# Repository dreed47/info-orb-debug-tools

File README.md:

# info-orb-debug-tools

- a version of info orb PCB that does not use pins 12, 13, 14, 15 and adds an IDC connector to connect a JTAG adapter for breakpoint debugging

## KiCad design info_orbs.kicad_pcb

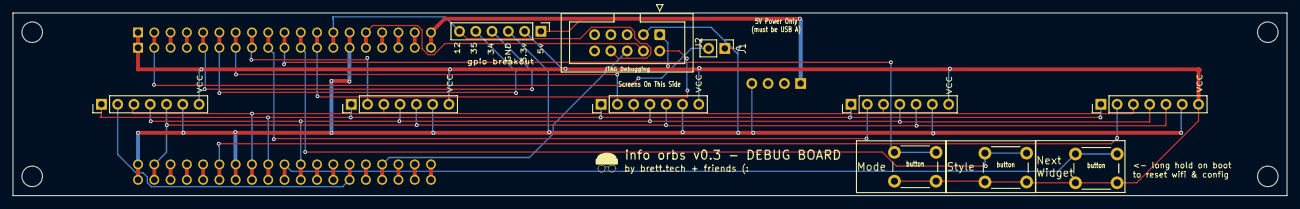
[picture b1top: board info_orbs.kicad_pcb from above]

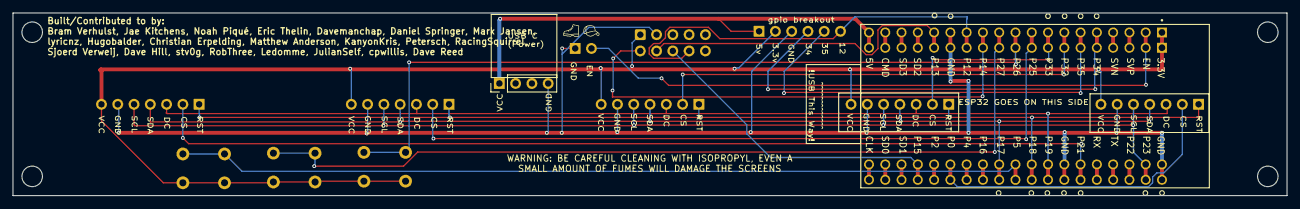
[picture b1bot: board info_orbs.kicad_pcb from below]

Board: 2 copper layers, 198.8 x 28.5 mm, 15 parts (3 on the bottom side), 36 nets.

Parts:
G*: LOGO; beaniegraphioc
J1: Conn_01x02_Pin; PinHeader_1x02_P2.54mm_Vertical
J2: AVR-JTAG-10; IDC-Header_2x05_P2.54mm_Vertical
SW1, SW2, SW3: SW_Push; SW_PUSH_6mm_H5mm
U1: PinHeader_1x06_P2.54mm_Vertical
USBPower1: PinHeader_1x04_P2.54mm_Vertical
V1: ESP32-DEVKITC-32D; 38 Pin Board
V2: ESP32-DEVKITC-32D; 38 Pin Board thin
tft1, tft2, tft3, tft4, tft5: PinHeader_1x07_P2.54mm_Vertical

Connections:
unnamed: J1.1, J2.3 (TDO), U1.3 (GND), USBPower1.4 (GND), V1.J2-14 (GND1), V1.J3-1 (GND3), V1.J3-7 (GND2), V2.J2-14 (GND1), V2.J3-1 (GND3), V2.J3-7 (GND2), tft1.6 (GND), tft2.6 (GND), tft3.6 (GND), tft4.6 (GND), tft5.6 (GND)
unnamed: J1.2, V1.J2-2 (EN), V2.J2-2 (EN)
unnamed: J2.1 (TCK), SW1.2, SW2.2, SW3.2, U1.2 (3.3v), V1.J2-1 (3V3), V2.J2-1 (3V3), tft1.7 (VCC), tft2.7 (VCC), tft3.7 (VCC), tft4.7 (VCC), tft5.7 (VCC)
unnamed: U1.4 (gipo34), V1.J2-5 (IO34), V2.J2-5 (IO34)
unnamed: J2.8 (~TRST), U1.6 (gpio12), V1.J2-13 (IO12), V2.J2-13 (IO12)
unnamed: U1.5 (gpio35), V1.J2-6 (IO35), V2.J2-6 (IO35)
unnamed: U1.1 (vcc), USBPower1.1 (VCC), V1.J2-19 (EXT_5V), V2.J2-19 (EXT_5V)
unnamed: V1.J3-19 (CLK), V2.J3-19 (CLK)
unnamed: V1.J2-18 (CMD), V2.J2-18 (CMD)
unnamed: V1.J3-14 (IO0), V2.J3-14 (IO0), tft1.2 (CS)
unnamed: V1.J3-15 (IO2), V2.J3-15 (IO2)
unnamed: V1.J3-13 (IO4), V2.J3-13 (IO4)
unnamed: SW3.1, V1.J3-10 (IO5), V2.J3-10 (IO5)
unnamed: J2.4 (VREF), V1.J2-15 (IO13), V2.J2-15 (IO13)
unnamed: J2.2 (GND), V1.J2-12 (IO14), V2.J2-12 (IO14)
unnamed: J2.6 (~SRST), V1.J3-16 (IO15), V2.J3-16 (IO15)
unnamed: V1.J3-12 (IO16), V2.J3-12 (IO16)
unnamed: V1.J3-11 (IO17), V2.J3-11 (IO17), tft1.4 (SDA), tft2.4 (SDA), tft3.4 (SDA), tft4.4 (SDA), tft5.4 (SDA)
unnamed: V1.J3-9 (IO18), V2.J3-9 (IO18), tft1.1 (RST), tft2.1 (RST), tft3.1 (RST), tft4.1 (RST), tft5.1 (RST)
unnamed: V1.J3-8 (IO19), V2.J3-8 (IO19), tft1.3 (DC), tft2.3 (DC), tft3.3 (DC), tft4.3 (DC), tft5.3 (DC)
unnamed: V1.J3-6 (IO21), V2.J3-6 (IO21), tft5.2 (CS)
unnamed: V1.J3-3 (IO22), V2.J3-3 (IO22)
unnamed: V1.J3-2 (IO23), V2.J3-2 (IO23), tft1.5 (SCL), tft2.5 (SCL), tft3.5 (SCL), tft4.5 (SCL), tft5.5 (SCL)
unnamed: V1.J2-9 (IO25), V2.J2-9 (IO25), tft4.2 (CS)
unnamed: SW1.1, V1.J2-10 (IO26), V2.J2-10 (IO26)
unnamed: SW2.1, V1.J2-11 (IO27), V2.J2-11 (IO27)
unnamed: V1.J2-7 (IO32), V2.J2-7 (IO32), tft3.2 (CS)
unnamed: V1.J2-8 (IO33), V2.J2-8 (IO33), tft2.2 (CS)
unnamed: V1.J3-5 (RXD0), V2.J3-5 (RXD0)
unnamed: V1.J3-18 (SD0), V2.J3-18 (SD0)
unnamed: V1.J3-17 (SD1), V2.J3-17 (SD1)
unnamed: V1.J2-16 (SD2), V2.J2-16 (SD2)
unnamed: V1.J2-17 (SD3), V2.J2-17 (SD3)
unnamed: V1.J2-4 (SENSOR_VN), V2.J2-4 (SENSOR_VN)
unnamed: V1.J2-3 (SENSOR_VP), V2.J2-3 (SENSOR_VP)
unnamed: V1.J3-4 (TXD0), V2.J3-4 (TXD0)
